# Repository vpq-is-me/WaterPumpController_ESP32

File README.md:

# Water pump controller.

This controller intended for control submersible pump installed in water well. It turn on pump when pressure in hydraulic accumulator (HA) dropped to lower pressure P1 and switch off when pressure rich high predefined pressure P2. Pressure measured by pressure transducer with range 0-6bar and output 4-20mA. 
For diagnostic reason there is water flow counter with pulse output - 1 pulse per 10litres (dry contact). 

In series with this controller installed external simple pressure switch (optional). It's aim is protection of system in case of controller failure. For normal work this pressure switch must tunned with upper disconnection pressure above controller's upper pressure P2. For exmple if controller's switch off pressure is 3.2 bar external pressure switch can be 3.5 bar. In case of controller failure or for test reason Bypass switch can be operated. It shorted controlle's output switch and in this case external pressure switch mantaine HA pressure.

This controller connected to Bluetooth MESH net and broadcast internal data, e.i. to [home_automation_server](https://github.com/vpq-is-me/home_auto_nodejs.git) (running on Raspberry Pi) for diagnostic and send message to Telegram bot in case of alarm.
 
Via Bluetooth MESH controller receive state of [Sewage Treatment System (STS)](https://github.com/vpq-is-me/SepticProtectionESP32.git) - (automomous canalization) and in case of STS overfill controller stops water feeding.

Also it stops water feeding in case of some failure:
   - dropped air pressure in Hydraulic Accumulator (air leak)
   - pump failure
   - pump capacity dropping 

### Entire system overview

### Controller circuit diagram

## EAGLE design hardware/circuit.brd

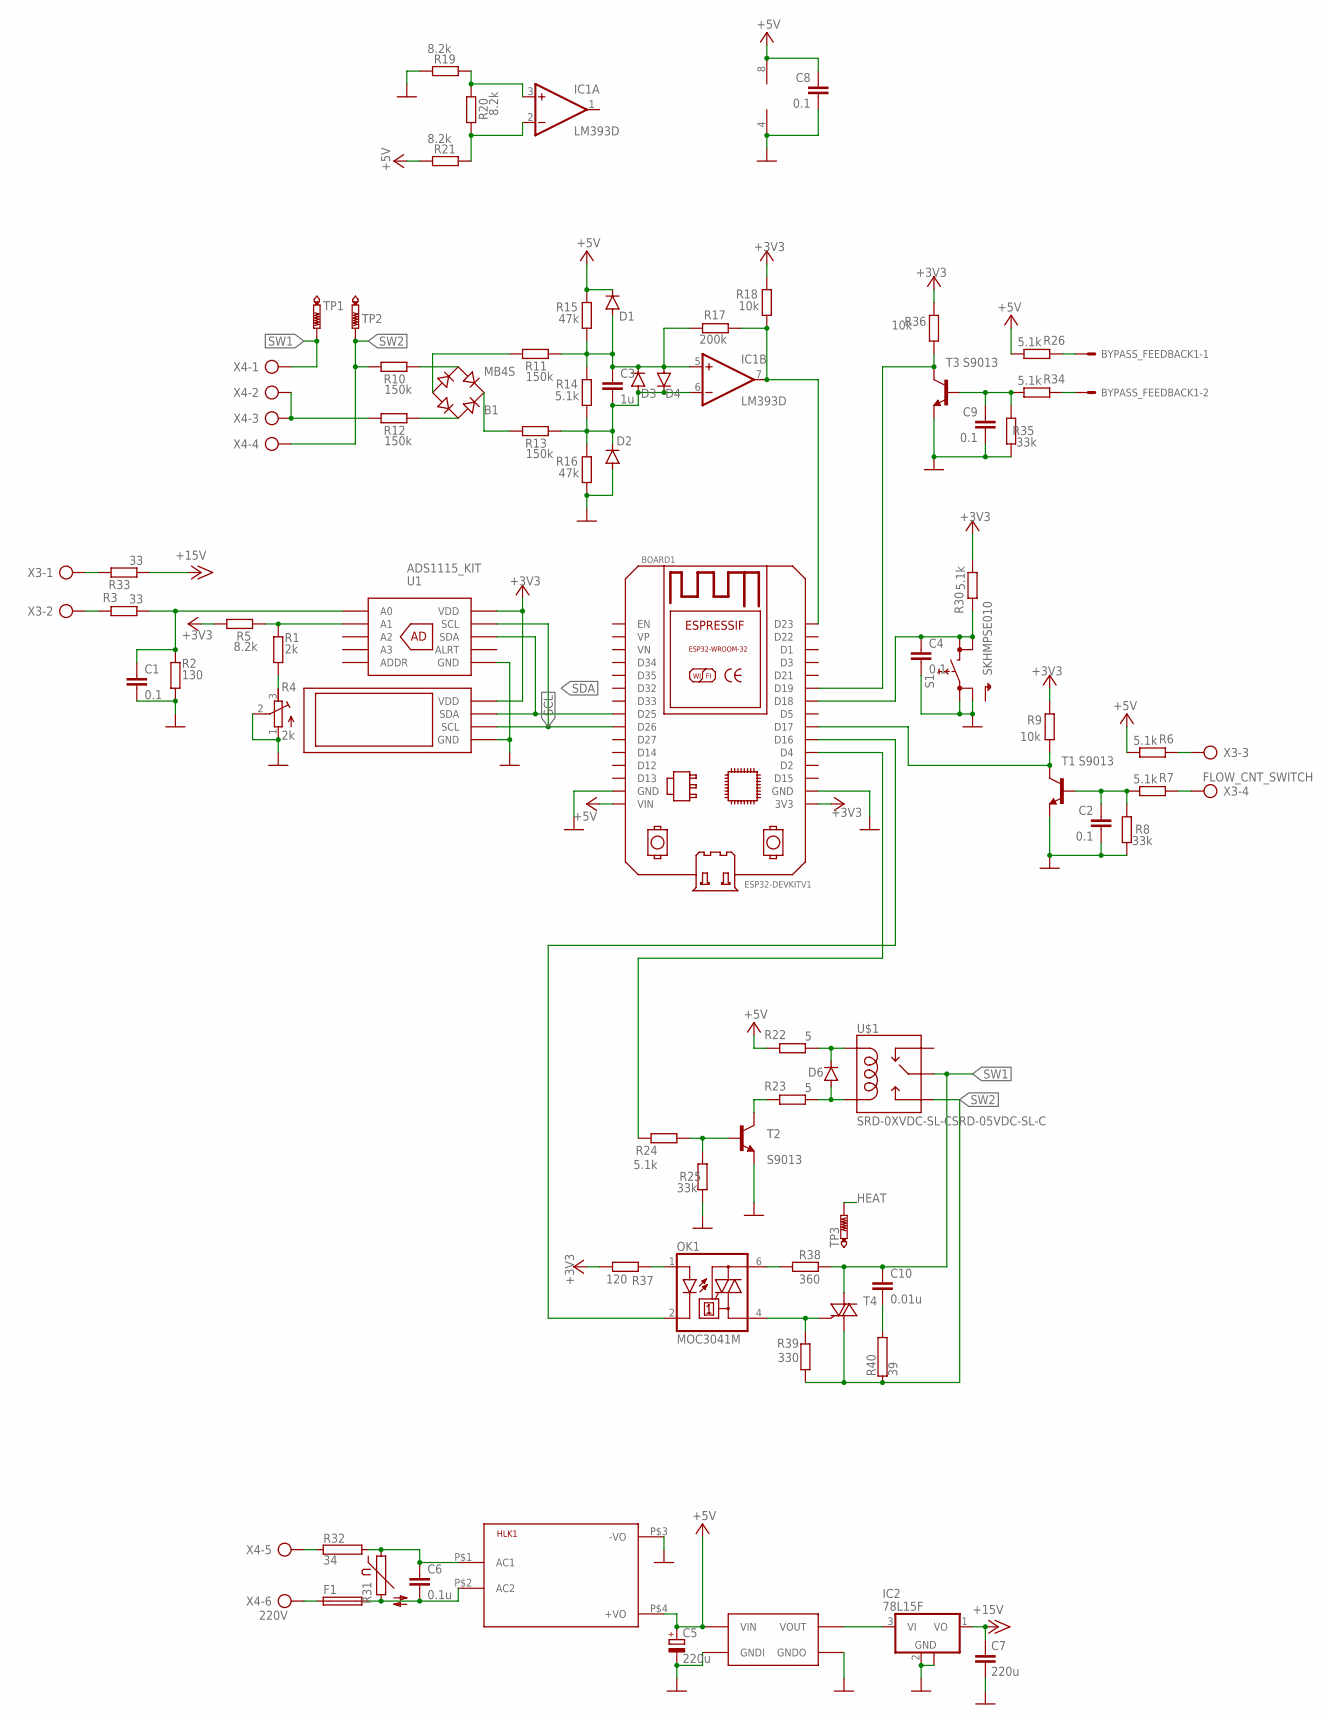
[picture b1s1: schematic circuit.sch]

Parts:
B1: MB4S; SOIC-4
BOARD1: ESP32DEVKITV1; ESP32-DEVKITV1
BYPASS_FEEDBACK1: C-GRID-02-70543; 70543-02
C1, C2, C4, C8, C9: 0.1; C1206
C3: 1u; C1206
C5: 220u; E3,5-8
C6: 0.1u; C10B5
C7: 220u; C1210K
C10: 0.01u; C10B5
D1, D2, D3, D4, D6: CGRM4001-G; SOD-123_MINI-SMA
DC1: HW-668_DC_DC_STEPUP
F1: FUSE19560; 19560
HLK1: HLK-PM013W; HLK-PM01
IC1: LM393D; SO08
IC2: 78L15F; SOT89
OK1: MOC3041M; DIL06
R1: 2k; R1206
R2: 130; R1206
R3, R33: 33; R1206
R4: 2k; RTRIM3202
R5, R19, R20, R21: 8.2k; R1206
R6, R7, R14, R24, R26, R30, R34: 5.1k; R1206
R8, R25, R35: 33k; R1206
R9, R18, R36: 10k; R1206
R10, R11, R12, R13: 150k; R1206
R15, R16: 47k; R1206
R17: 200k; R1206
R22, R23: 5; R1206
R31: S10K510
R32: 34; CA0001
R37: 120; R1206
R38: 360; R1206
R39: 330; R1206
R40: 39; CA0001
S1: SKHMPSE010; SKHMPXE010
T1, T2, T3: S9013; SOT23-BEC
T4: BT136; TO220AB
TP1, TP2: PTR1PAD1-20Y; P1-20Y
TP3: PTR1B1,27; B1,27
U1: ADS1115_KIT
U2: SSD1306_OLED
U$1: SRD-0XVDC-SL-CSRD-05VDC-SL-C; SRD-0XVDC-SL-C
X3: FLOW_CNT_SWITCH; AK300/4
X4: 220V; AK300/6

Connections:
+3V3: BOARD1.3V3, R5.2, R9.1, R18.1, R30.1, R36.1, R37.1, U1.P$1 (VDD), U2.P$3 (VDD)
+5V: BOARD1.VIN, C5.+, C8.1, D1.C, DC1.P$1 (VIN), HLK1.P$4 (+VO), IC1.8 (V+), R6.1, R15.1, R21.1, R22.2, R26.1
+15V: C7.1, IC2.1 (VO), R33.1
FLOW_SW: BOARD1.D17, R9.2, T1.C
GND: BOARD1.GND, BOARD1.GND@1 (GND), C1.2, C2.2, C4.2, C5.-, C7.2, C8.2, C9.2, D2.A, DC1.P$2 (GNDI), DC1.P$3 (GNDO), HLK1.P$3 (-VO), IC1.4 (V-), IC2.2 (GND), IC2.2@1 (GND), R2.1, R4.1 (A), R4.2 (S), R8.2, R16.2, R19.1, R25.2, R35.2, S1.1 (1.1), S1.2 (1.2), T1.E, T2.E, T3.E, U1.P$2 (GND), U2.P$4 (GND)
HEAT: TP3.TP
unnamed: C9.1, R34.1, R35.1, T3.B
unnamed: BYPASS_FEEDBACK1.1, R26.2
unnamed: C1.1, R2.2, R3.1, U1.P$7 (A0)
unnamed: R1.2, R5.1, U1.P$8 (A1)
unnamed: R1.1, R4.3 (E)
unnamed: C2.1, R7.1, R8.1, T1.B
unnamed: R33.2, X3.1
unnamed: B1.+, R13.2
unnamed: C3.2, D2.C, D3.A, D4.C, IC1.6 (-IN), R13.1, R14.2, R16.1
unnamed: C3.1, D1.A, D3.C, D4.A, IC1.5 (+IN), R11.1, R14.1, R15.2, R17.1
unnamed: B1.-, R11.2
unnamed: R32.1, X4.5
unnamed: B1.~2 (AC2), R10.1
unnamed: B1.~1 (AC1), R12.1
unnamed: R23.2, T2.C
unnamed: IC1.3 (+IN), R19.2, R20.1
unnamed: IC1.2 (-IN), R20.2, R21.2
unnamed: D6.C, R22.1, U$1.COIL1
unnamed: F1.1, X4.6
unnamed: R3.2, X3.2
unnamed: BYPASS_FEEDBACK1.2, R34.2
unnamed: R24.1, R25.1, T2.B
unnamed: R12.2, X4.2, X4.3
unnamed: R6.2, X3.3
unnamed: C6.1, HLK1.P$1 (AC1), R31.1, R32.2
unnamed: C6.2, F1.2, HLK1.P$2 (AC2), R31.2
unnamed: D6.A, R23.1, U$1.COIL0
unnamed: DC1.P$4 (VOUT), IC2.3 (VI)
unnamed: R7.2, X3.4
unnamed: BOARD1.D19, R36.2, T3.C
unnamed: BOARD1.D16, OK1.2 (C)
unnamed: OK1.1 (A), R37.2
unnamed: OK1.6 (A2), R38.1
unnamed: OK1.4 (A1), R39.2, T4.3 (G)
unnamed: C10.2, R40.2
PP_ON: BOARD1.D23, IC1.7 (OUT), R17.2, R18.2
RST_ALR: BOARD1.D18, C4.1, R30.2, S1.3 (2.1), S1.4 (2.2)
SCL: BOARD1.D26, U1.P$3 (SCL), U2.P$2 (SCL)
SDA: BOARD1.D25, U1.P$4 (SDA), U2.P$1 (SDA)
SSRELAY_ON: BOARD1.D4, R24.2
SW1: C10.1, R38.2, T4.2 (A2), TP1.TP, U$1.SWCOMMON, X4.1
SW2: R10.2, R39.1, R40.1, T4.1 (A1), TP2.TP, U$1.SWOPEN, X4.4

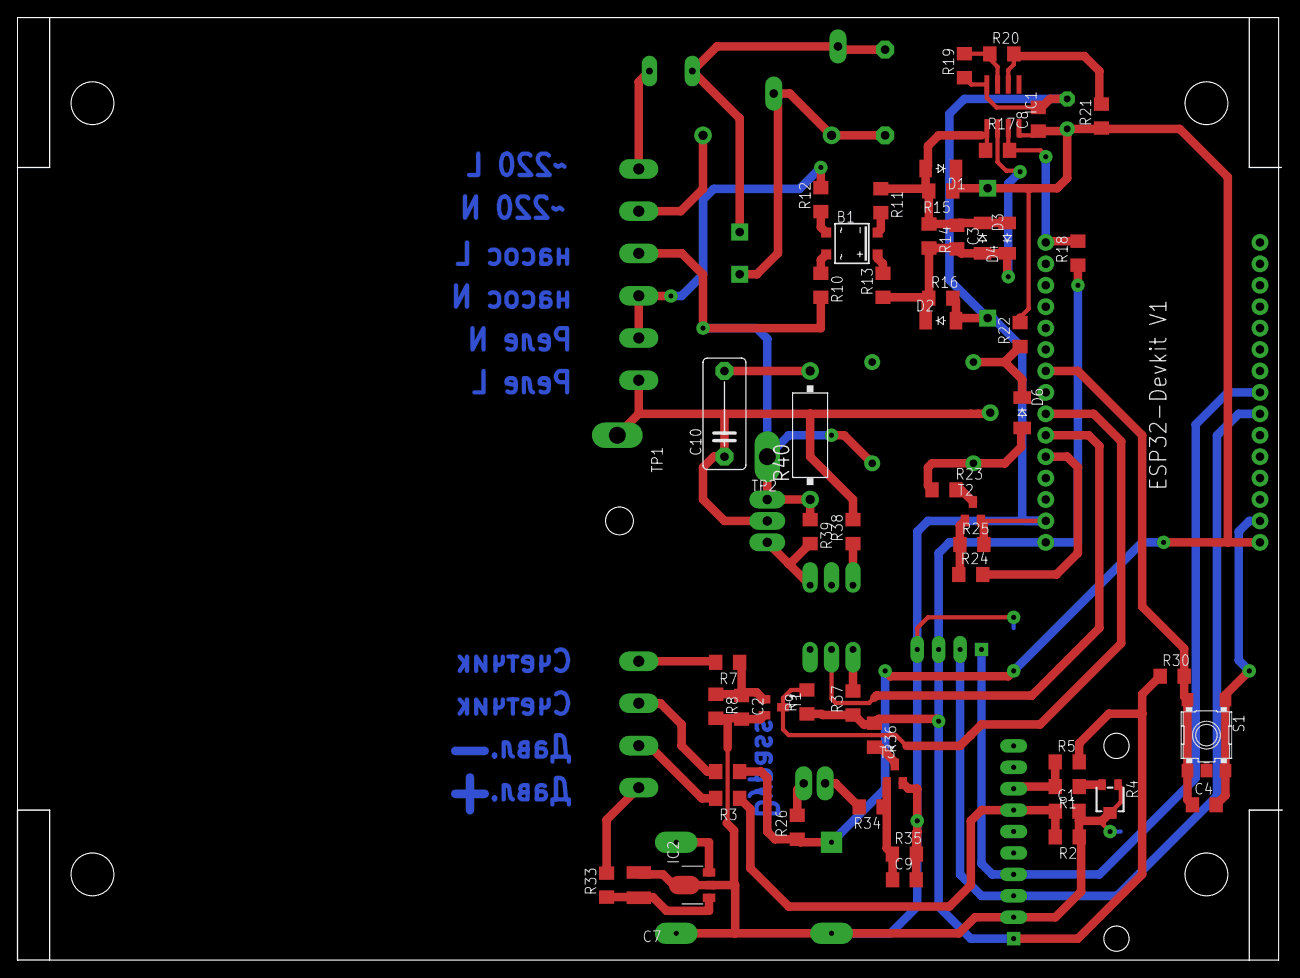
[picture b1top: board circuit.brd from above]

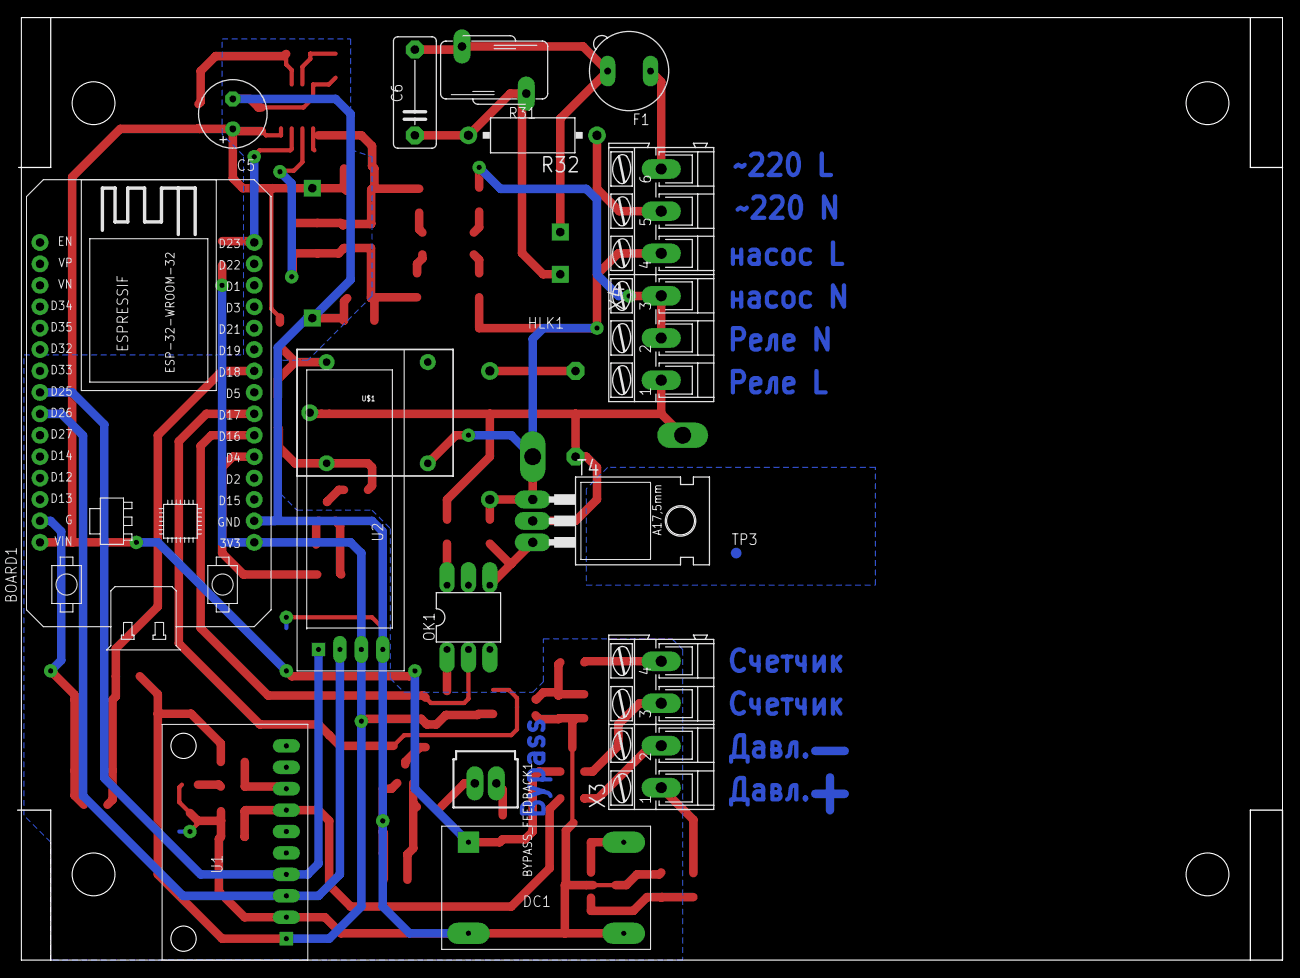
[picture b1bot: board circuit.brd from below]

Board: 2 copper layers, 149.5 x 111.8 mm, 74 parts (17 on the bottom side), 47 nets.

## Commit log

2023-02-27 v0_1
2023-03-18 Added calculation of flow using pump head vs capacity data from datasheet
2023-04-09 Stable version before "septic" can receive
2023-04-13 Added reception info from septic Output power (?) increased First 'total time' after power on is negative
2023-12-07 working state
2024-04-04 add system description
2024-04-04 edit readme
